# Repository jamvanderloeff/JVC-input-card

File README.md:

# JVC input card
 A compatible clone input card for JVC (and some Ikegami and Panasonic) professional CRT monitors

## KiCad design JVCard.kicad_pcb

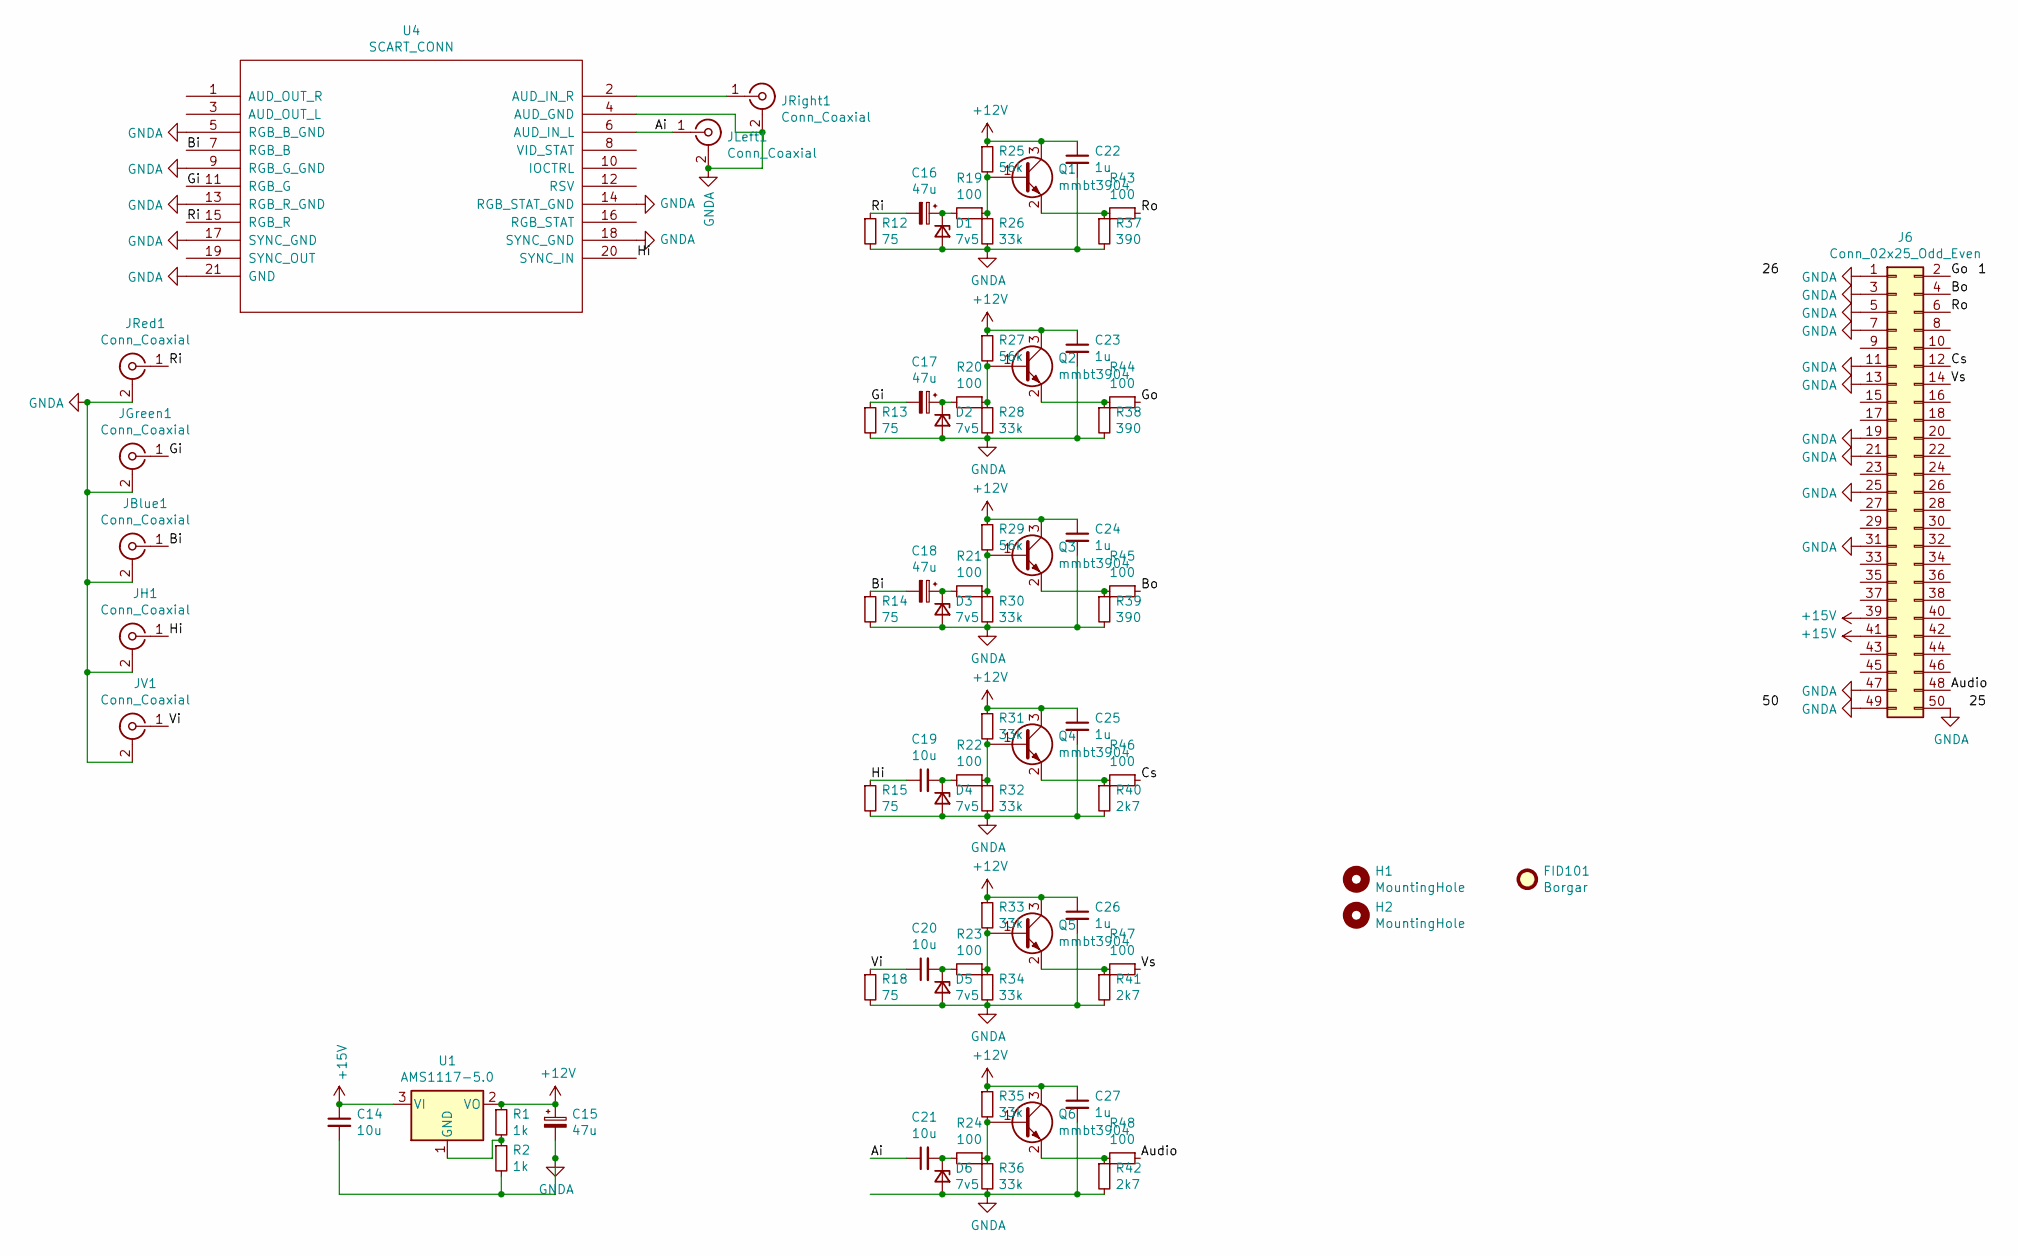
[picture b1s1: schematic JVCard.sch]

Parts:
C14, C19, C20, C21: 10u; C_0805_2012Metric_Pad1.15x1.40mm_HandSolder; LCSC C15850
C15, C16, C17, C18: 47u; CP_Elec_6.3x7.7; LCSC C249976
C22, C23, C24, C25, C26, C27: 1u; C_0805_2012Metric_Pad1.15x1.40mm_HandSolder; LCSC C28323
D1, D2, D3, D4, D5, D6: 7v5; D_SOD-123F; LCSC C123796
FID101: Borgar; borgar
H1, H2: MountingHole; MountingHole_3.2mm_M3; LCSC NOT FITTED
J6: Conn_02x25_Odd_Even; PinHeader_2x25_P2.54mm_Horizontal; LCSC NOT FITTED
JBlue1: Conn_Coaxial; BNC_Amphenol_B6252HB-NPP3G-50_Horizontal; LCSC NOT FITTED
JGreen1: Conn_Coaxial; BNC_Amphenol_B6252HB-NPP3G-50_Horizontal; LCSC NOT FITTED
JH1: Conn_Coaxial; BNC_Amphenol_B6252HB-NPP3G-50_Horizontal; LCSC NOT FITTED
JLeft1: Conn_Coaxial; Cheapo_RCA_single_edge; LCSC NOT FITTED
JRed1: Conn_Coaxial; BNC_Amphenol_B6252HB-NPP3G-50_Horizontal; LCSC NOT FITTED
JRight1: Conn_Coaxial; Cheapo_RCA_single_edge; LCSC NOT FITTED
JV1: Conn_Coaxial; BNC_Amphenol_B6252HB-NPP3G-50_Horizontal; LCSC NOT FITTED
Q1, Q2, Q3, Q4, Q5, Q6: mmbt3904; SOT-23; LCSC C20526
R1, R2: 1k; R_0805_2012Metric_Pad1.15x1.40mm_HandSolder; LCSC C17513
R12, R13, R14, R15, R18: 75; R_0805_2012Metric_Pad1.15x1.40mm_HandSolder; LCSC C20638
R19, R20, R21, R22, R23, R24, R43, R44, R45, R46, R47, R48: 100; R_0805_2012Metric_Pad1.15x1.40mm_HandSolder; LCSC C17408
R25, R27, R29: 56k; R_0805_2012Metric_Pad1.15x1.40mm_HandSolder; LCSC C17756
R26, R28, R30, R31, R32, R33, R34, R35, R36: 33k; R_0805_2012Metric_Pad1.15x1.40mm_HandSolder; LCSC C17633
R37, R38, R39: 390; R_0805_2012Metric_Pad1.15x1.40mm_HandSolder; LCSC C17655
R40, R41, R42: 2k7; R_0805_2012Metric_Pad1.15x1.40mm_HandSolder; LCSC C17530
U1: AMS1117-5.0; SOT-223-3_TabPin2; LCSC C6187
U4: SCART_CONN; LCSC NOT FITTED

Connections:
+12V: C15.1, C22.1, C23.1, C24.1, C25.1, C26.1, C27.1, Q1.3 (C), Q2.3 (C), Q3.3 (C), Q4.3 (C), Q5.3 (C), Q6.3 (C), R1.1, R25.1, R27.1, R29.1, R31.1, R33.1, R35.1, U1.2 (VO)
+15V: C14.1, J6.39, J6.41, U1.3 (VI)
/Ai: C21.1, JLeft1.1 (In), U4.6 (AUD_IN_L)
/Audio: J6.48, R48.1
/Bi: C18.2, JBlue1.1 (In), R14.1, U4.7 (RGB_B)
/Bo: J6.4, R45.1
/Cs: J6.12, R46.1
/Gi: C17.2, JGreen1.1 (In), R13.1, U4.11 (RGB_G)
/Go: J6.2, R44.1
/Hi: C19.1, JH1.1 (In), R15.1, U4.20 (SYNC_IN)
/Ri: C16.2, JRed1.1 (In), R12.1, U4.15 (RGB_R)
/Ro: J6.6, R43.1
/Vi: C20.1, JV1.1 (In), R18.1
/Vs: J6.14, R47.1
GNDA: C14.2, C15.2, C22.2, C23.2, C24.2, C25.2, C26.2, C27.2, D1.2 (A), D2.2 (A), D3.2 (A), D4.2 (A), D5.2 (A), D6.2 (A), J6.1, J6.3, J6.5, J6.7, J6.11, J6.13, J6.19, J6.21, J6.25, J6.31, J6.47, J6.49, J6.50, JBlue1.2 (Ext), JGreen1.2 (Ext), JH1.2 (Ext), JLeft1.2 (Ext), JRed1.2 (Ext), JRight1.2 (Ext), JV1.2 (Ext), R2.2, R12.2, R13.2, R14.2, R15.2, R18.2, R26.2, R28.2, R30.2, R32.2, R34.2, R36.2, R37.2, R38.2, R39.2, R40.2, R41.2, R42.2, U4.4 (AUD_GND), U4.5 (RGB_B_GND), U4.9 (RGB_G_GND), U4.13 (RGB_R_GND), U4.14 (RGB_STAT_GND), U4.17 (SYNC_GND), U4.18 (SYNC_GND), U4.21 (GND)
unnamed: C16.1, D1.1 (K), R19.2
unnamed: C17.1, D2.1 (K), R20.2
unnamed: C18.1, D3.1 (K), R21.2
unnamed: C19.2, D4.1 (K), R22.2
unnamed: C20.2, D5.1 (K), R23.2
unnamed: C21.2, D6.1 (K), R24.2
unnamed: JRight1.1 (In), U4.2 (AUD_IN_R)
unnamed: Q1.1 (B), R19.1, R25.2, R26.1
unnamed: Q1.2 (E), R37.1, R43.2
unnamed: Q2.1 (B), R20.1, R27.2, R28.1
unnamed: Q2.2 (E), R38.1, R44.2
unnamed: Q3.1 (B), R21.1, R29.2, R30.1
unnamed: Q3.2 (E), R39.1, R45.2
unnamed: Q4.1 (B), R22.1, R31.2, R32.1
unnamed: Q4.2 (E), R40.1, R46.2
unnamed: Q5.1 (B), R23.1, R33.2, R34.1
unnamed: Q5.2 (E), R41.1, R47.2
unnamed: Q6.1 (B), R24.1, R35.2, R36.1
unnamed: Q6.2 (E), R42.1, R48.2
unnamed: R1.2, R2.1, U1.1 (GND)

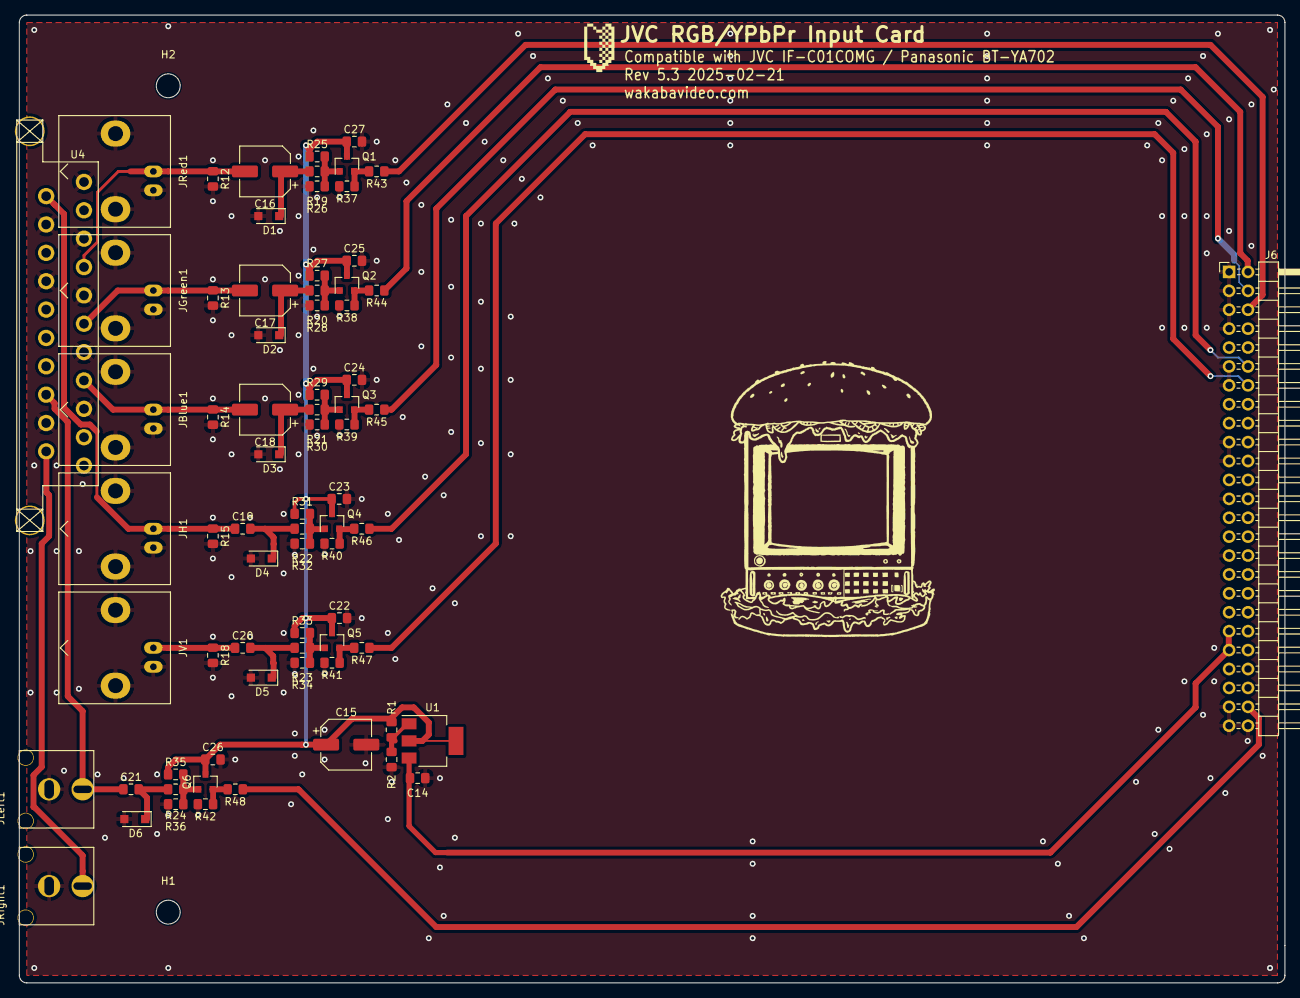
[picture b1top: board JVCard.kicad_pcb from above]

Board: 2 copper layers, 170.0 x 130.0 mm, 75 parts (0 on the bottom side), 35 nets.

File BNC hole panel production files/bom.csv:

Designator,Footprint,Quantity,Value,LCSC Part #
"C14_2, C14, C19_2, C19, C20_2, C20, C21_2, C21",0805,8,10u,
"C15_2, C15, C16_2, C16, C17_2, C17, C18_2, C18",CP_Elec_6.3x7.7,8,47u,
"C22_2, C22, C23_2, C23, C24_2, C24, C25_2, C25, C26_2, C26, C27_2, C27",0805,12,1u,
"D1_2, D1, D2_2, D2, D3_2, D3, D4_2, D4, D5_2, D5, D6_2, D6",D_SOD-123F,12,7v5,
"J6_2, J6",PinHeader_2x25_P2.54mm_Horizontal,2,Conn_02x25_Odd_Even,
"JBlue1_2, JBlue1, JGreen1_2, JGreen1, JH1_2, JH1, JRed1_2, JRed1, JV1_2, JV1",BNC_Amphenol_B6252HB-NPP3G-50_Horizontal_smallerpads,10,Conn_Coaxial,
"JLeft1_2, JLeft1, JRight1_2, JRight1",Cheapo_RCA_single_edge,4,Conn_Coaxial,
"Q1_2, Q1, Q2_2, Q2, Q3_2, Q3, Q4_2, Q4, Q5_2, Q5, Q6_2, Q6",SOT-23,12,mmbt3904,
"R1_2, R1, R2_2, R2",0805,4,1k,
"R12_2, R12, R13_2, R13, R14_2, R14, R15_2, R15, R18_2, R18",0805,10,75,
"R19_2, R19, R20_2, R20, R21_2, R21, R22_2, R22, R23_2, R23, R24_2, R24, R43_2, R43, R44_2, R44, R45_2, R45, R46_2, R46, R47_2, R47, R48_2, R48",0805,24,100,
"R25_2, R25, R27_2, R27, R29_2, R29",0805,6,56k,
"R26_2, R26, R28_2, R28, R30_2, R30, R31_2, R31, R32_2, R32, R33_2, R33, R34_2, R34, R35_2, R35, R36_2, R36",0805,18,33k,
"R37_2, R37, R38_2, R38, R39_2, R39",0805,6,390,
"R40_2, R40, R41_2, R41, R42_2, R42",0805,6,2k7,
"U1_2, U1",SOT-223-3_TabPin2,2,AMS1117-5.0,
"U4_2, U4",SCART_CONN,2,SCART_CONN,

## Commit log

2020-03-12 Initial commit, design rev 5.1
2020-03-12 add manufacture files
2020-03-27 fixed regularot pinout whoops
2020-04-02 fix resistor too
2020-05-08 Create JVCard.step
    3d model because why not
2020-05-09 Create .gitignore
    ignore bak
2020-05-18 draft scart-vga inside
2020-06-06 add rear panel
2020-07-09 4 way panelised
2021-10-04 resync
2021-10-04 fix reg in bom
2022-09-16 migrate to kicad 6, panel covering extended a little
2022-09-16 gerbs for cover panels updated
2024-09-12 new gerbers for BNC and SCART hole plates
2024-10-15 updated production files
2025-02-20 updated kicad version, parts and fab file updates
2025-02-21 prod files
